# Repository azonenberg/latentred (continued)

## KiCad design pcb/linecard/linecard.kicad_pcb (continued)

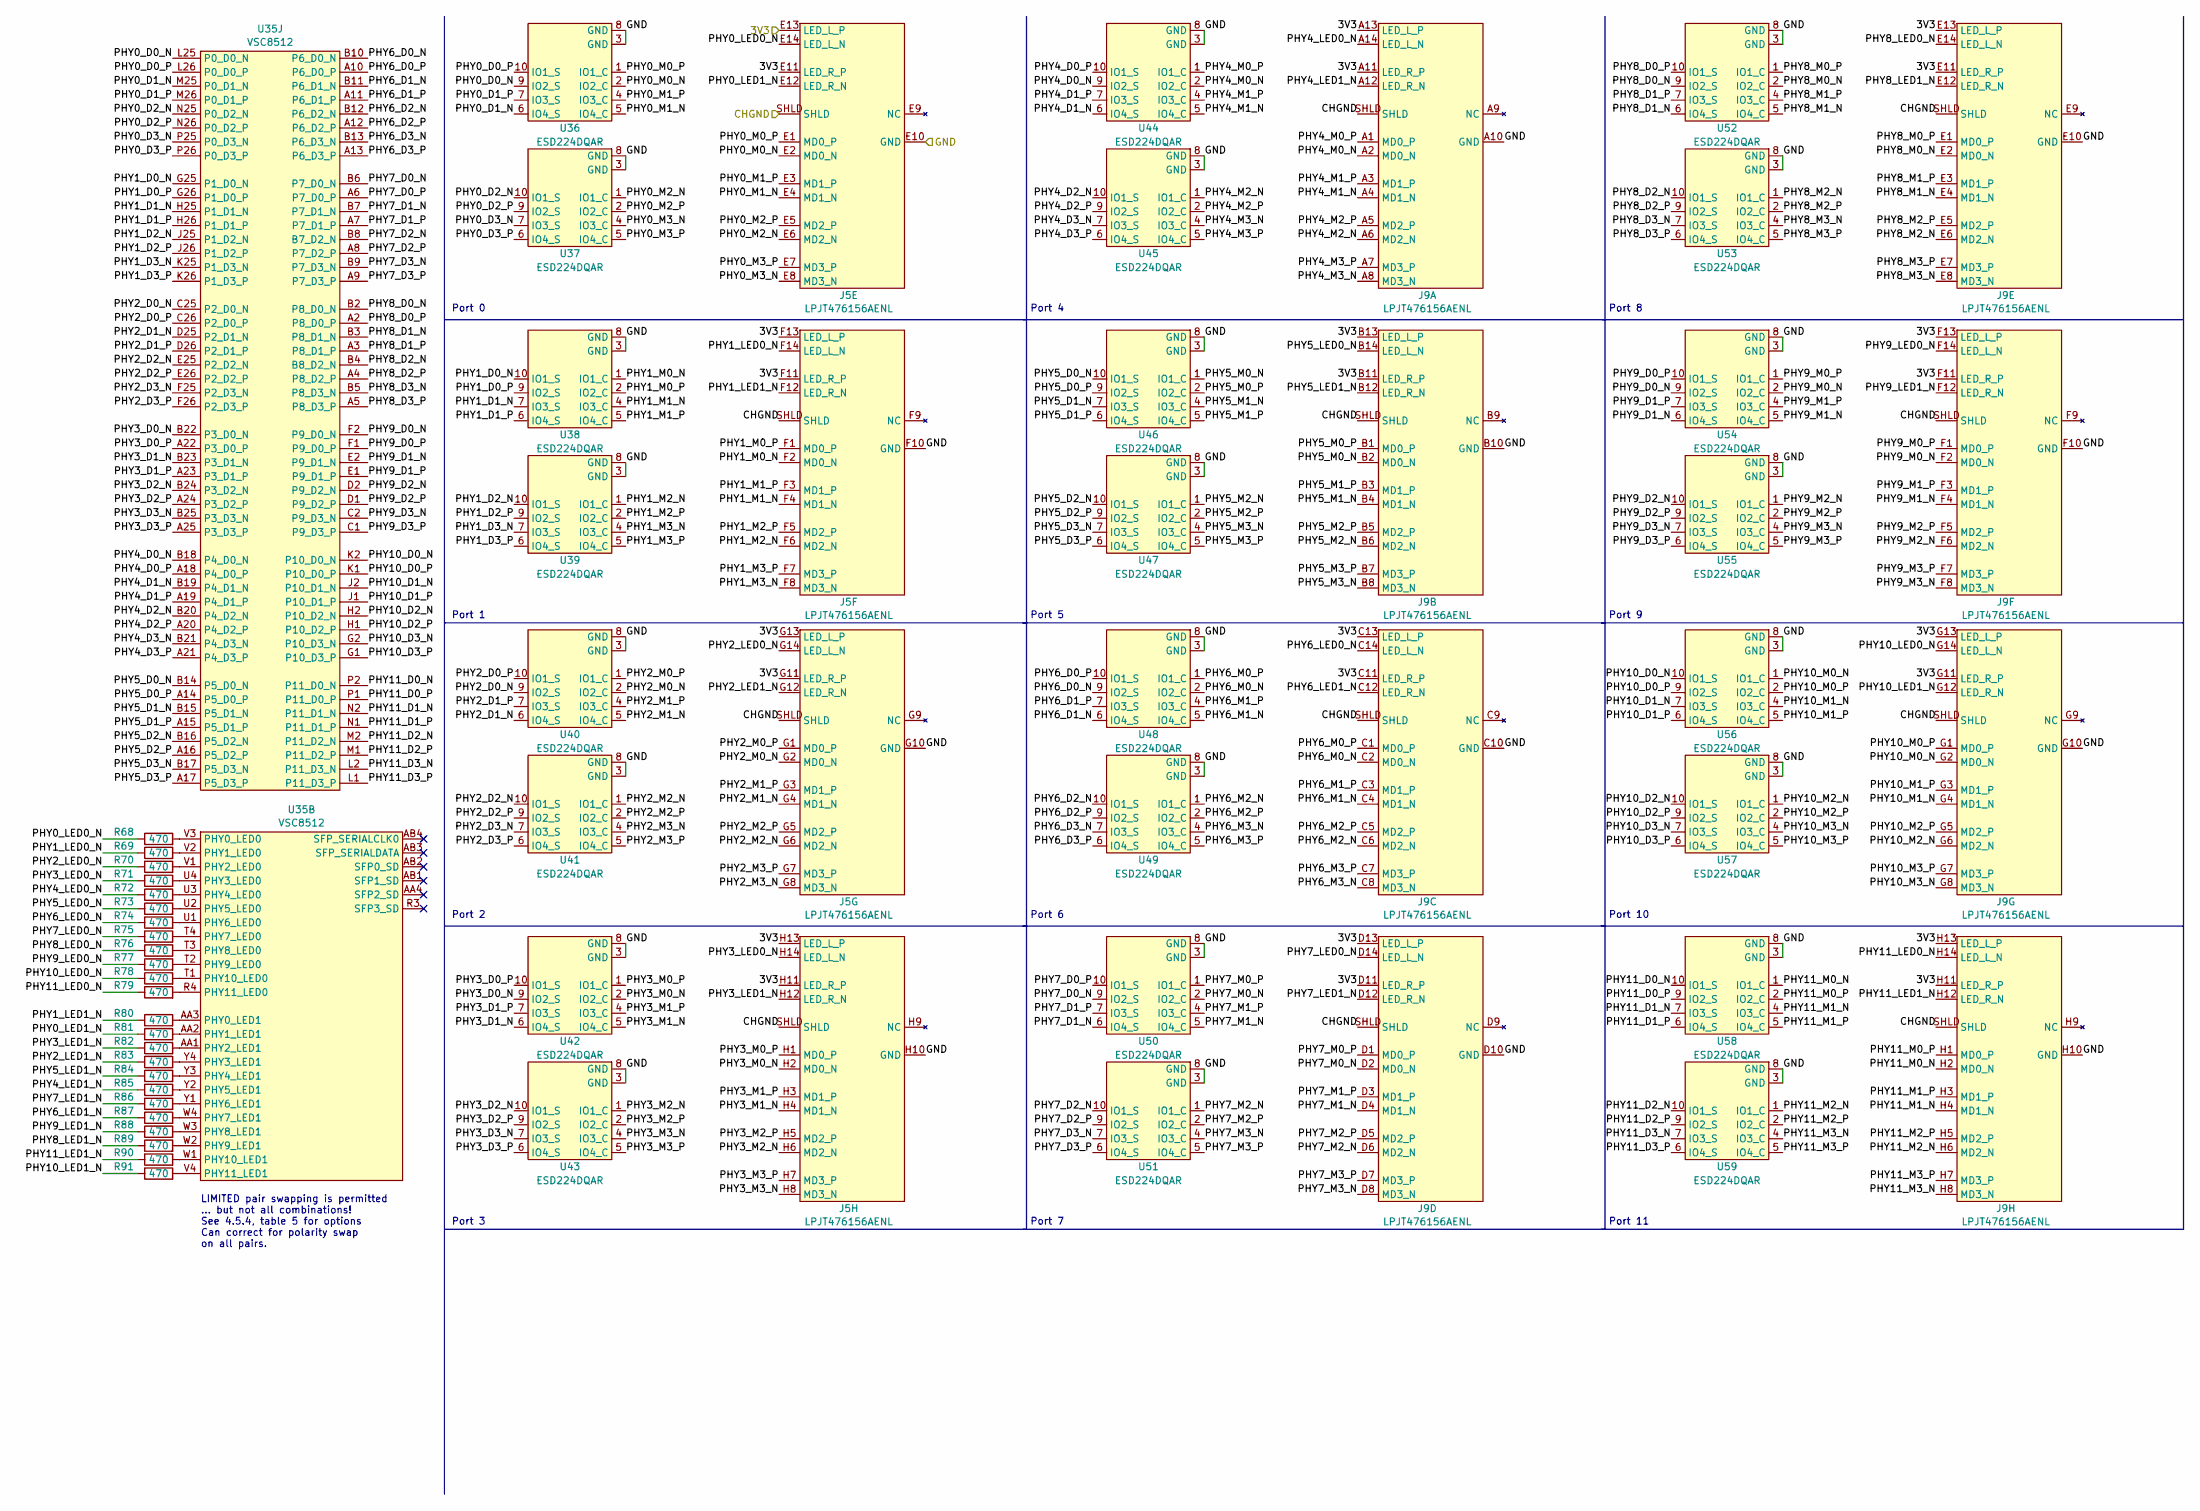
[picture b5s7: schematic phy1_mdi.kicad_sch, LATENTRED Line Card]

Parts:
J5, J9: LPJT476156AENL; CONN_LINKPP_LPJT476156AENL
R68, R69, R70, R71, R72, R73, R74, R75, R76, R77, R78, R79, R80, R81, R82, R83, R84, R85, R86, R87, R88, R89, R90, R91: 470; EIA_0402_RES_NOSILK
U35: VSC8512; BGA_676_27x27_FULLARRAY_1MM_FFG676
U36, U37, U38, U39, U40, U41, U42, U43, U44, U45, U46, U47, U48, U49, U50, U51, U52, U53, U54, U55, U56, U57, U58, U59: ESD224DQAR; DFN_10_0.5MM_2.5x1MM_TI_DQA

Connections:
/3V3: J5.E11 (LED_R_P), J5.E13 (LED_L_P), J5.F11 (LED_R_P), J5.F13 (LED_L_P), J5.G11 (LED_R_P), J5.G13 (LED_L_P), J5.H11 (LED_R_P), J5.H13 (LED_L_P), J9.A11 (LED_R_P), J9.A13 (LED_L_P), J9.B11 (LED_R_P), J9.B13 (LED_L_P), J9.C11 (LED_R_P), J9.C13 (LED_L_P), J9.D11 (LED_R_P), J9.D13 (LED_L_P), J9.E11 (LED_R_P), J9.E13 (LED_L_P), J9.F11 (LED_R_P), J9.F13 (LED_L_P), J9.G11 (LED_R_P), J9.G13 (LED_L_P), J9.H11 (LED_R_P), J9.H13 (LED_L_P); also elsewhere on the board
/PHY 1 MDI/PHY0_D0_N: U35.L25 (P0_D0_N), U36.9 (IO2_S)
/PHY 1 MDI/PHY0_D0_P: U35.L26 (P0_D0_P), U36.10 (IO1_S)
/PHY 1 MDI/PHY0_D1_N: U35.M25 (P0_D1_N), U36.6 (IO4_S)
/PHY 1 MDI/PHY0_D1_P: U35.M26 (P0_D1_P), U36.7 (IO3_S)
/PHY 1 MDI/PHY0_D2_N: U35.N25 (P0_D2_N), U37.10 (IO1_S)
/PHY 1 MDI/PHY0_D2_P: U35.N26 (P0_D2_P), U37.9 (IO2_S)
/PHY 1 MDI/PHY0_D3_N: U35.P25 (P0_D3_N), U37.7 (IO3_S)
/PHY 1 MDI/PHY0_D3_P: U35.P26 (P0_D3_P), U37.6 (IO4_S)
/PHY 1 MDI/PHY0_LED0_N: J5.E14 (LED_L_N), R68.1
/PHY 1 MDI/PHY0_LED1_N: J5.E12 (LED_R_N), R81.1
/PHY 1 MDI/PHY0_M0_N: J5.E2 (MD0_N), U36.2 (IO2_C)
/PHY 1 MDI/PHY0_M0_P: J5.E1 (MD0_P), U36.1 (IO1_C)
/PHY 1 MDI/PHY0_M1_N: J5.E4 (MD1_N), U36.5 (IO4_C)
/PHY 1 MDI/PHY0_M1_P: J5.E3 (MD1_P), U36.4 (IO3_C)
/PHY 1 MDI/PHY0_M2_N: J5.E6 (MD2_N), U37.1 (IO1_C)
/PHY 1 MDI/PHY0_M2_P: J5.E5 (MD2_P), U37.2 (IO2_C)
/PHY 1 MDI/PHY0_M3_N: J5.E8 (MD3_N), U37.4 (IO3_C)
/PHY 1 MDI/PHY0_M3_P: J5.E7 (MD3_P), U37.5 (IO4_C)
/PHY 1 MDI/PHY1_D0_N: U35.G25 (P1_D0_N), U38.10 (IO1_S)
/PHY 1 MDI/PHY1_D0_P: U35.G26 (P1_D0_P), U38.9 (IO2_S)
/PHY 1 MDI/PHY1_D1_N: U35.H25 (P1_D1_N), U38.7 (IO3_S)
/PHY 1 MDI/PHY1_D1_P: U35.H26 (P1_D1_P), U38.6 (IO4_S)
/PHY 1 MDI/PHY1_D2_N: U35.J25 (P1_D2_N), U39.10 (IO1_S)
/PHY 1 MDI/PHY1_D2_P: U35.J26 (P1_D2_P), U39.9 (IO2_S)
/PHY 1 MDI/PHY1_D3_N: U35.K25 (P1_D3_N), U39.7 (IO3_S)
/PHY 1 MDI/PHY1_D3_P: U35.K26 (P1_D3_P), U39.6 (IO4_S)
/PHY 1 MDI/PHY1_LED0_N: J5.F14 (LED_L_N), R69.1
/PHY 1 MDI/PHY1_LED1_N: J5.F12 (LED_R_N), R80.1
/PHY 1 MDI/PHY1_M0_N: J5.F2 (MD0_N), U38.1 (IO1_C)
/PHY 1 MDI/PHY1_M0_P: J5.F1 (MD0_P), U38.2 (IO2_C)
/PHY 1 MDI/PHY1_M1_N: J5.F4 (MD1_N), U38.4 (IO3_C)
/PHY 1 MDI/PHY1_M1_P: J5.F3 (MD1_P), U38.5 (IO4_C)
/PHY 1 MDI/PHY1_M2_N: J5.F6 (MD2_N), U39.1 (IO1_C)
/PHY 1 MDI/PHY1_M2_P: J5.F5 (MD2_P), U39.2 (IO2_C)
/PHY 1 MDI/PHY1_M3_N: J5.F8 (MD3_N), U39.4 (IO3_C)
/PHY 1 MDI/PHY1_M3_P: J5.F7 (MD3_P), U39.5 (IO4_C)
/PHY 1 MDI/PHY2_D0_N: U35.C25 (P2_D0_N), U40.9 (IO2_S)
/PHY 1 MDI/PHY2_D0_P: U35.C26 (P2_D0_P), U40.10 (IO1_S)
/PHY 1 MDI/PHY2_D1_N: U35.D25 (P2_D1_N), U40.6 (IO4_S)
/PHY 1 MDI/PHY2_D1_P: U35.D26 (P2_D1_P), U40.7 (IO3_S)
/PHY 1 MDI/PHY2_D2_N: U35.E25 (P2_D2_N), U41.10 (IO1_S)
/PHY 1 MDI/PHY2_D2_P: U35.E26 (P2_D2_P), U41.9 (IO2_S)
/PHY 1 MDI/PHY2_D3_N: U35.F25 (P2_D3_N), U41.7 (IO3_S)
/PHY 1 MDI/PHY2_D3_P: U35.F26 (P2_D3_P), U41.6 (IO4_S)
/PHY 1 MDI/PHY2_LED0_N: J5.G14 (LED_L_N), R70.1
/PHY 1 MDI/PHY2_LED1_N: J5.G12 (LED_R_N), R83.1
/PHY 1 MDI/PHY2_M0_N: J5.G2 (MD0_N), U40.2 (IO2_C)
/PHY 1 MDI/PHY2_M0_P: J5.G1 (MD0_P), U40.1 (IO1_C)
/PHY 1 MDI/PHY2_M1_N: J5.G4 (MD1_N), U40.5 (IO4_C)
/PHY 1 MDI/PHY2_M1_P: J5.G3 (MD1_P), U40.4 (IO3_C)
/PHY 1 MDI/PHY2_M2_N: J5.G6 (MD2_N), U41.1 (IO1_C)
/PHY 1 MDI/PHY2_M2_P: J5.G5 (MD2_P), U41.2 (IO2_C)
/PHY 1 MDI/PHY2_M3_N: J5.G8 (MD3_N), U41.4 (IO3_C)
/PHY 1 MDI/PHY2_M3_P: J5.G7 (MD3_P), U41.5 (IO4_C)
/PHY 1 MDI/PHY3_D0_N: U35.B22 (P3_D0_N), U42.9 (IO2_S)
/PHY 1 MDI/PHY3_D0_P: U35.A22 (P3_D0_P), U42.10 (IO1_S)
/PHY 1 MDI/PHY3_D1_N: U35.B23 (P3_D1_N), U42.6 (IO4_S)
/PHY 1 MDI/PHY3_D1_P: U35.A23 (P3_D1_P), U42.7 (IO3_S)
/PHY 1 MDI/PHY3_D2_N: U35.B24 (P3_D2_N), U43.10 (IO1_S)
/PHY 1 MDI/PHY3_D2_P: U35.A24 (P3_D2_P), U43.9 (IO2_S)
/PHY 1 MDI/PHY3_D3_N: U35.B25 (P3_D3_N), U43.7 (IO3_S)
/PHY 1 MDI/PHY3_D3_P: U35.A25 (P3_D3_P), U43.6 (IO4_S)
/PHY 1 MDI/PHY3_LED0_N: J5.H14 (LED_L_N), R71.1
/PHY 1 MDI/PHY3_LED1_N: J5.H12 (LED_R_N), R82.1
/PHY 1 MDI/PHY3_M0_N: J5.H2 (MD0_N), U42.2 (IO2_C)
/PHY 1 MDI/PHY3_M0_P: J5.H1 (MD0_P), U42.1 (IO1_C)
/PHY 1 MDI/PHY3_M1_N: J5.H4 (MD1_N), U42.5 (IO4_C)
/PHY 1 MDI/PHY3_M1_P: J5.H3 (MD1_P), U42.4 (IO3_C)
/PHY 1 MDI/PHY3_M2_N: J5.H6 (MD2_N), U43.1 (IO1_C)
/PHY 1 MDI/PHY3_M2_P: J5.H5 (MD2_P), U43.2 (IO2_C)
/PHY 1 MDI/PHY3_M3_N: J5.H8 (MD3_N), U43.4 (IO3_C)
/PHY 1 MDI/PHY3_M3_P: J5.H7 (MD3_P), U43.5 (IO4_C)
/PHY 1 MDI/PHY4_D0_N: U35.B18 (P4_D0_N), U44.9 (IO2_S)
/PHY 1 MDI/PHY4_D0_P: U35.A18 (P4_D0_P), U44.10 (IO1_S)
/PHY 1 MDI/PHY4_D1_N: U35.B19 (P4_D1_N), U44.6 (IO4_S)
/PHY 1 MDI/PHY4_D1_P: U35.A19 (P4_D1_P), U44.7 (IO3_S)
/PHY 1 MDI/PHY4_D2_N: U35.B20 (P4_D2_N), U45.10 (IO1_S)
/PHY 1 MDI/PHY4_D2_P: U35.A20 (P4_D2_P), U45.9 (IO2_S)
/PHY 1 MDI/PHY4_D3_N: U35.B21 (P4_D3_N), U45.7 (IO3_S)
/PHY 1 MDI/PHY4_D3_P: U35.A21 (P4_D3_P), U45.6 (IO4_S)
/PHY 1 MDI/PHY4_LED0_N: J9.A14 (LED_L_N), R72.1
/PHY 1 MDI/PHY4_LED1_N: J9.A12 (LED_R_N), R85.1
/PHY 1 MDI/PHY4_M0_N: J9.A2 (MD0_N), U44.2 (IO2_C)
/PHY 1 MDI/PHY4_M0_P: J9.A1 (MD0_P), U44.1 (IO1_C)
/PHY 1 MDI/PHY4_M1_N: J9.A4 (MD1_N), U44.5 (IO4_C)
/PHY 1 MDI/PHY4_M1_P: J9.A3 (MD1_P), U44.4 (IO3_C)
/PHY 1 MDI/PHY4_M2_N: J9.A6 (MD2_N), U45.1 (IO1_C)
/PHY 1 MDI/PHY4_M2_P: J9.A5 (MD2_P), U45.2 (IO2_C)
/PHY 1 MDI/PHY4_M3_N: J9.A8 (MD3_N), U45.4 (IO3_C)
/PHY 1 MDI/PHY4_M3_P: J9.A7 (MD3_P), U45.5 (IO4_C)
/PHY 1 MDI/PHY5_D0_N: U35.B14 (P5_D0_N), U46.10 (IO1_S)
/PHY 1 MDI/PHY5_D0_P: U35.A14 (P5_D0_P), U46.9 (IO2_S)
/PHY 1 MDI/PHY5_D1_N: U35.B15 (P5_D1_N), U46.7 (IO3_S)
/PHY 1 MDI/PHY5_D1_P: U35.A15 (P5_D1_P), U46.6 (IO4_S)
/PHY 1 MDI/PHY5_D2_N: U35.B16 (P5_D2_N), U47.10 (IO1_S)
/PHY 1 MDI/PHY5_D2_P: U35.A16 (P5_D2_P), U47.9 (IO2_S)
/PHY 1 MDI/PHY5_D3_N: U35.B17 (P5_D3_N), U47.7 (IO3_S)
/PHY 1 MDI/PHY5_D3_P: U35.A17 (P5_D3_P), U47.6 (IO4_S)
/PHY 1 MDI/PHY5_LED0_N: J9.B14 (LED_L_N), R73.1
/PHY 1 MDI/PHY5_LED1_N: J9.B12 (LED_R_N), R84.1
/PHY 1 MDI/PHY5_M0_N: J9.B2 (MD0_N), U46.1 (IO1_C)
/PHY 1 MDI/PHY5_M0_P: J9.B1 (MD0_P), U46.2 (IO2_C)
/PHY 1 MDI/PHY5_M1_N: J9.B4 (MD1_N), U46.4 (IO3_C)
/PHY 1 MDI/PHY5_M1_P: J9.B3 (MD1_P), U46.5 (IO4_C)
/PHY 1 MDI/PHY5_M2_N: J9.B6 (MD2_N), U47.1 (IO1_C)
/PHY 1 MDI/PHY5_M2_P: J9.B5 (MD2_P), U47.2 (IO2_C)
/PHY 1 MDI/PHY5_M3_N: J9.B8 (MD3_N), U47.4 (IO3_C)
/PHY 1 MDI/PHY5_M3_P: J9.B7 (MD3_P), U47.5 (IO4_C)
/PHY 1 MDI/PHY6_D0_N: U35.B10 (P6_D0_N), U48.9 (IO2_S)
/PHY 1 MDI/PHY6_D0_P: U35.A10 (P6_D0_P), U48.10 (IO1_S)
/PHY 1 MDI/PHY6_D1_N: U35.B11 (P6_D1_N), U48.6 (IO4_S)
/PHY 1 MDI/PHY6_D1_P: U35.A11 (P6_D1_P), U48.7 (IO3_S)
/PHY 1 MDI/PHY6_D2_N: U35.B12 (P6_D2_N), U49.10 (IO1_S)
/PHY 1 MDI/PHY6_D2_P: U35.A12 (P6_D2_P), U49.9 (IO2_S)
/PHY 1 MDI/PHY6_D3_N: U35.B13 (P6_D3_N), U49.7 (IO3_S)
/PHY 1 MDI/PHY6_D3_P: U35.A13 (P6_D3_P), U49.6 (IO4_S)
/PHY 1 MDI/PHY6_LED0_N: J9.C14 (LED_L_N), R74.1
/PHY 1 MDI/PHY6_LED1_N: J9.C12 (LED_R_N), R87.1
/PHY 1 MDI/PHY6_M0_N: J9.C2 (MD0_N), U48.2 (IO2_C)
/PHY 1 MDI/PHY6_M0_P: J9.C1 (MD0_P), U48.1 (IO1_C)
/PHY 1 MDI/PHY6_M1_N: J9.C4 (MD1_N), U48.5 (IO4_C)
/PHY 1 MDI/PHY6_M1_P: J9.C3 (MD1_P), U48.4 (IO3_C)
/PHY 1 MDI/PHY6_M2_N: J9.C6 (MD2_N), U49.1 (IO1_C)
/PHY 1 MDI/PHY6_M2_P: J9.C5 (MD2_P), U49.2 (IO2_C)
/PHY 1 MDI/PHY6_M3_N: J9.C8 (MD3_N), U49.4 (IO3_C)
/PHY 1 MDI/PHY6_M3_P: J9.C7 (MD3_P), U49.5 (IO4_C)
/PHY 1 MDI/PHY7_D0_N: U35.B6 (P7_D0_N), U50.9 (IO2_S)
/PHY 1 MDI/PHY7_D0_P: U35.A6 (P7_D0_P), U50.10 (IO1_S)
/PHY 1 MDI/PHY7_D1_N: U35.B7 (P7_D1_N), U50.6 (IO4_S)
/PHY 1 MDI/PHY7_D1_P: U35.A7 (P7_D1_P), U50.7 (IO3_S)
/PHY 1 MDI/PHY7_D2_N: U35.B8 (B7_D2_N), U51.10 (IO1_S)
/PHY 1 MDI/PHY7_D2_P: U35.A8 (P7_D2_P), U51.9 (IO2_S)
/PHY 1 MDI/PHY7_D3_N: U35.B9 (P7_D3_N), U51.7 (IO3_S)
/PHY 1 MDI/PHY7_D3_P: U35.A9 (P7_D3_P), U51.6 (IO4_S)
/PHY 1 MDI/PHY7_LED0_N: J9.D14 (LED_L_N), R75.1
/PHY 1 MDI/PHY7_LED1_N: J9.D12 (LED_R_N), R86.1
/PHY 1 MDI/PHY7_M0_N: J9.D2 (MD0_N), U50.2 (IO2_C)
/PHY 1 MDI/PHY7_M0_P: J9.D1 (MD0_P), U50.1 (IO1_C)
/PHY 1 MDI/PHY7_M1_N: J9.D4 (MD1_N), U50.5 (IO4_C)
/PHY 1 MDI/PHY7_M1_P: J9.D3 (MD1_P), U50.4 (IO3_C)
/PHY 1 MDI/PHY7_M2_N: J9.D6 (MD2_N), U51.1 (IO1_C)
/PHY 1 MDI/PHY7_M2_P: J9.D5 (MD2_P), U51.2 (IO2_C)
/PHY 1 MDI/PHY7_M3_N: J9.D8 (MD3_N), U51.4 (IO3_C)
/PHY 1 MDI/PHY7_M3_P: J9.D7 (MD3_P), U51.5 (IO4_C)
/PHY 1 MDI/PHY8_D0_N: U35.B2 (P8_D0_N), U52.9 (IO2_S)
/PHY 1 MDI/PHY8_D0_P: U35.A2 (P8_D0_P), U52.10 (IO1_S)
/PHY 1 MDI/PHY8_D1_N: U35.B3 (P8_D1_N), U52.6 (IO4_S)
/PHY 1 MDI/PHY8_D1_P: U35.A3 (P8_D1_P), U52.7 (IO3_S)
/PHY 1 MDI/PHY8_D2_N: U35.B4 (B8_D2_N), U53.10 (IO1_S)
/PHY 1 MDI/PHY8_D2_P: U35.A4 (P8_D2_P), U53.9 (IO2_S)
/PHY 1 MDI/PHY8_D3_N: U35.B5 (P8_D3_N), U53.7 (IO3_S)
/PHY 1 MDI/PHY8_D3_P: U35.A5 (P8_D3_P), U53.6 (IO4_S)
/PHY 1 MDI/PHY8_LED0_N: J9.E14 (LED_L_N), R76.1
/PHY 1 MDI/PHY8_LED1_N: J9.E12 (LED_R_N), R89.1
/PHY 1 MDI/PHY8_M0_N: J9.E2 (MD0_N), U52.2 (IO2_C)
/PHY 1 MDI/PHY8_M0_P: J9.E1 (MD0_P), U52.1 (IO1_C)
/PHY 1 MDI/PHY8_M1_N: J9.E4 (MD1_N), U52.5 (IO4_C)
/PHY 1 MDI/PHY8_M1_P: J9.E3 (MD1_P), U52.4 (IO3_C)
/PHY 1 MDI/PHY8_M2_N: J9.E6 (MD2_N), U53.1 (IO1_C)
/PHY 1 MDI/PHY8_M2_P: J9.E5 (MD2_P), U53.2 (IO2_C)
/PHY 1 MDI/PHY8_M3_N: J9.E8 (MD3_N), U53.4 (IO3_C)
/PHY 1 MDI/PHY8_M3_P: J9.E7 (MD3_P), U53.5 (IO4_C)
/PHY 1 MDI/PHY9_D0_N: U35.F2 (P9_D0_N), U54.9 (IO2_S)
/PHY 1 MDI/PHY9_D0_P: U35.F1 (P9_D0_P), U54.10 (IO1_S)
/PHY 1 MDI/PHY9_D1_N: U35.E2 (P9_D1_N), U54.6 (IO4_S)
/PHY 1 MDI/PHY9_D1_P: U35.E1 (P9_D1_P), U54.7 (IO3_S)
/PHY 1 MDI/PHY9_D2_N: U35.D2 (P9_D2_N), U55.10 (IO1_S)
/PHY 1 MDI/PHY9_D2_P: U35.D1 (P9_D2_P), U55.9 (IO2_S)
/PHY 1 MDI/PHY9_D3_N: U35.C2 (P9_D3_N), U55.7 (IO3_S)
/PHY 1 MDI/PHY9_D3_P: U35.C1 (P9_D3_P), U55.6 (IO4_S)
/PHY 1 MDI/PHY9_LED0_N: J9.F14 (LED_L_N), R77.1
/PHY 1 MDI/PHY9_LED1_N: J9.F12 (LED_R_N), R88.1
/PHY 1 MDI/PHY9_M0_N: J9.F2 (MD0_N), U54.2 (IO2_C)
/PHY 1 MDI/PHY9_M0_P: J9.F1 (MD0_P), U54.1 (IO1_C)
/PHY 1 MDI/PHY9_M1_N: J9.F4 (MD1_N), U54.5 (IO4_C)
/PHY 1 MDI/PHY9_M1_P: J9.F3 (MD1_P), U54.4 (IO3_C)
/PHY 1 MDI/PHY9_M2_N: J9.F6 (MD2_N), U55.1 (IO1_C)
/PHY 1 MDI/PHY9_M2_P: J9.F5 (MD2_P), U55.2 (IO2_C)
/PHY 1 MDI/PHY9_M3_N: J9.F8 (MD3_N), U55.4 (IO3_C)
/PHY 1 MDI/PHY9_M3_P: J9.F7 (MD3_P), U55.5 (IO4_C)
/PHY 1 MDI/PHY10_D0_N: U35.K2 (P10_D0_N), U56.10 (IO1_S)
/PHY 1 MDI/PHY10_D0_P: U35.K1 (P10_D0_P), U56.9 (IO2_S)
/PHY 1 MDI/PHY10_D1_N: U35.J2 (P10_D1_N), U56.7 (IO3_S)
/PHY 1 MDI/PHY10_D1_P: U35.J1 (P10_D1_P), U56.6 (IO4_S)
/PHY 1 MDI/PHY10_D2_N: U35.H2 (P10_D2_N), U57.10 (IO1_S)
/PHY 1 MDI/PHY10_D2_P: U35.H1 (P10_D2_P), U57.9 (IO2_S)
/PHY 1 MDI/PHY10_D3_N: U35.G2 (P10_D3_N), U57.7 (IO3_S)
/PHY 1 MDI/PHY10_D3_P: U35.G1 (P10_D3_P), U57.6 (IO4_S)
/PHY 1 MDI/PHY10_LED0_N: J9.G14 (LED_L_N), R78.1
/PHY 1 MDI/PHY10_LED1_N: J9.G12 (LED_R_N), R91.1
/PHY 1 MDI/PHY10_M0_N: J9.G2 (MD0_N), U56.1 (IO1_C)
/PHY 1 MDI/PHY10_M0_P: J9.G1 (MD0_P), U56.2 (IO2_C)
/PHY 1 MDI/PHY10_M1_N: J9.G4 (MD1_N), U56.4 (IO3_C)
/PHY 1 MDI/PHY10_M1_P: J9.G3 (MD1_P), U56.5 (IO4_C)
/PHY 1 MDI/PHY10_M2_N: J9.G6 (MD2_N), U57.1 (IO1_C)
/PHY 1 MDI/PHY10_M2_P: J9.G5 (MD2_P), U57.2 (IO2_C)
/PHY 1 MDI/PHY10_M3_N: J9.G8 (MD3_N), U57.4 (IO3_C)
/PHY 1 MDI/PHY10_M3_P: J9.G7 (MD3_P), U57.5 (IO4_C)
/PHY 1 MDI/PHY11_D0_N: U35.P2 (P11_D0_N), U58.10 (IO1_S)
/PHY 1 MDI/PHY11_D0_P: U35.P1 (P11_D0_P), U58.9 (IO2_S)
/PHY 1 MDI/PHY11_D1_N: U35.N2 (P11_D1_N), U58.7 (IO3_S)
/PHY 1 MDI/PHY11_D1_P: U35.N1 (P11_D1_P), U58.6 (IO4_S)
/PHY 1 MDI/PHY11_D2_N: U35.M2 (P11_D2_N), U59.10 (IO1_S)
/PHY 1 MDI/PHY11_D2_P: U35.M1 (P11_D2_P), U59.9 (IO2_S)
/PHY 1 MDI/PHY11_D3_N: U35.L2 (P11_D3_N), U59.7 (IO3_S)
/PHY 1 MDI/PHY11_D3_P: U35.L1 (P11_D3_P), U59.6 (IO4_S)
/PHY 1 MDI/PHY11_LED0_N: J9.H14 (LED_L_N), R79.1
/PHY 1 MDI/PHY11_LED1_N: J9.H12 (LED_R_N), R90.1
/PHY 1 MDI/PHY11_M0_N: J9.H2 (MD0_N), U58.1 (IO1_C)
/PHY 1 MDI/PHY11_M0_P: J9.H1 (MD0_P), U58.2 (IO2_C)
/PHY 1 MDI/PHY11_M1_N: J9.H4 (MD1_N), U58.4 (IO3_C)
/PHY 1 MDI/PHY11_M1_P: J9.H3 (MD1_P), U58.5 (IO4_C)
/PHY 1 MDI/PHY11_M2_N: J9.H6 (MD2_N), U59.1 (IO1_C)
/PHY 1 MDI/PHY11_M2_P: J9.H5 (MD2_P), U59.2 (IO2_C)
/PHY 1 MDI/PHY11_M3_N: J9.H8 (MD3_N), U59.4 (IO3_C)
/PHY 1 MDI/PHY11_M3_P: J9.H7 (MD3_P), U59.5 (IO4_C)
unnamed: R68.2, U35.V3 (PHY0_LED0)
unnamed: R80.2, U35.AA3 (PHY0_LED1)
unnamed: R69.2, U35.V2 (PHY1_LED0)
unnamed: R81.2, U35.AA2 (PHY1_LED1)
unnamed: R70.2, U35.V1 (PHY2_LED0)
unnamed: R82.2, U35.AA1 (PHY2_LED1)
unnamed: R71.2, U35.U4 (PHY3_LED0)
unnamed: R83.2, U35.Y4 (PHY3_LED1)
unnamed: R72.2, U35.U3 (PHY4_LED0)
unnamed: R84.2, U35.Y3 (PHY4_LED1)
unnamed: R73.2, U35.U2 (PHY5_LED0)
unnamed: R85.2, U35.Y2 (PHY5_LED1)
unnamed: R74.2, U35.U1 (PHY6_LED0)
unnamed: R86.2, U35.Y1 (PHY6_LED1)
unnamed: R75.2, U35.T4 (PHY7_LED0)
unnamed: R87.2, U35.W4 (PHY7_LED1)
unnamed: R76.2, U35.T3 (PHY8_LED0)
unnamed: R88.2, U35.W3 (PHY8_LED1)
unnamed: R77.2, U35.T2 (PHY9_LED0)
unnamed: R89.2, U35.W2 (PHY9_LED1)
unnamed: R78.2, U35.T1 (PHY10_LED0)
unnamed: R90.2, U35.W1 (PHY10_LED1)
unnamed: R79.2, U35.R4 (PHY11_LED0)
unnamed: R91.2, U35.V4 (PHY11_LED1)

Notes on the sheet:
Port 1
LIMITED pair swapping is permitted ... but not all combinations! See 4.5.4, table 5 for options Can correct for polarity swap on all pairs.
Port 6
Port 0
Port 8
Port 4
Port 10
Port 11
Port 9
Port 2
Port 3
Port 5
Port 7

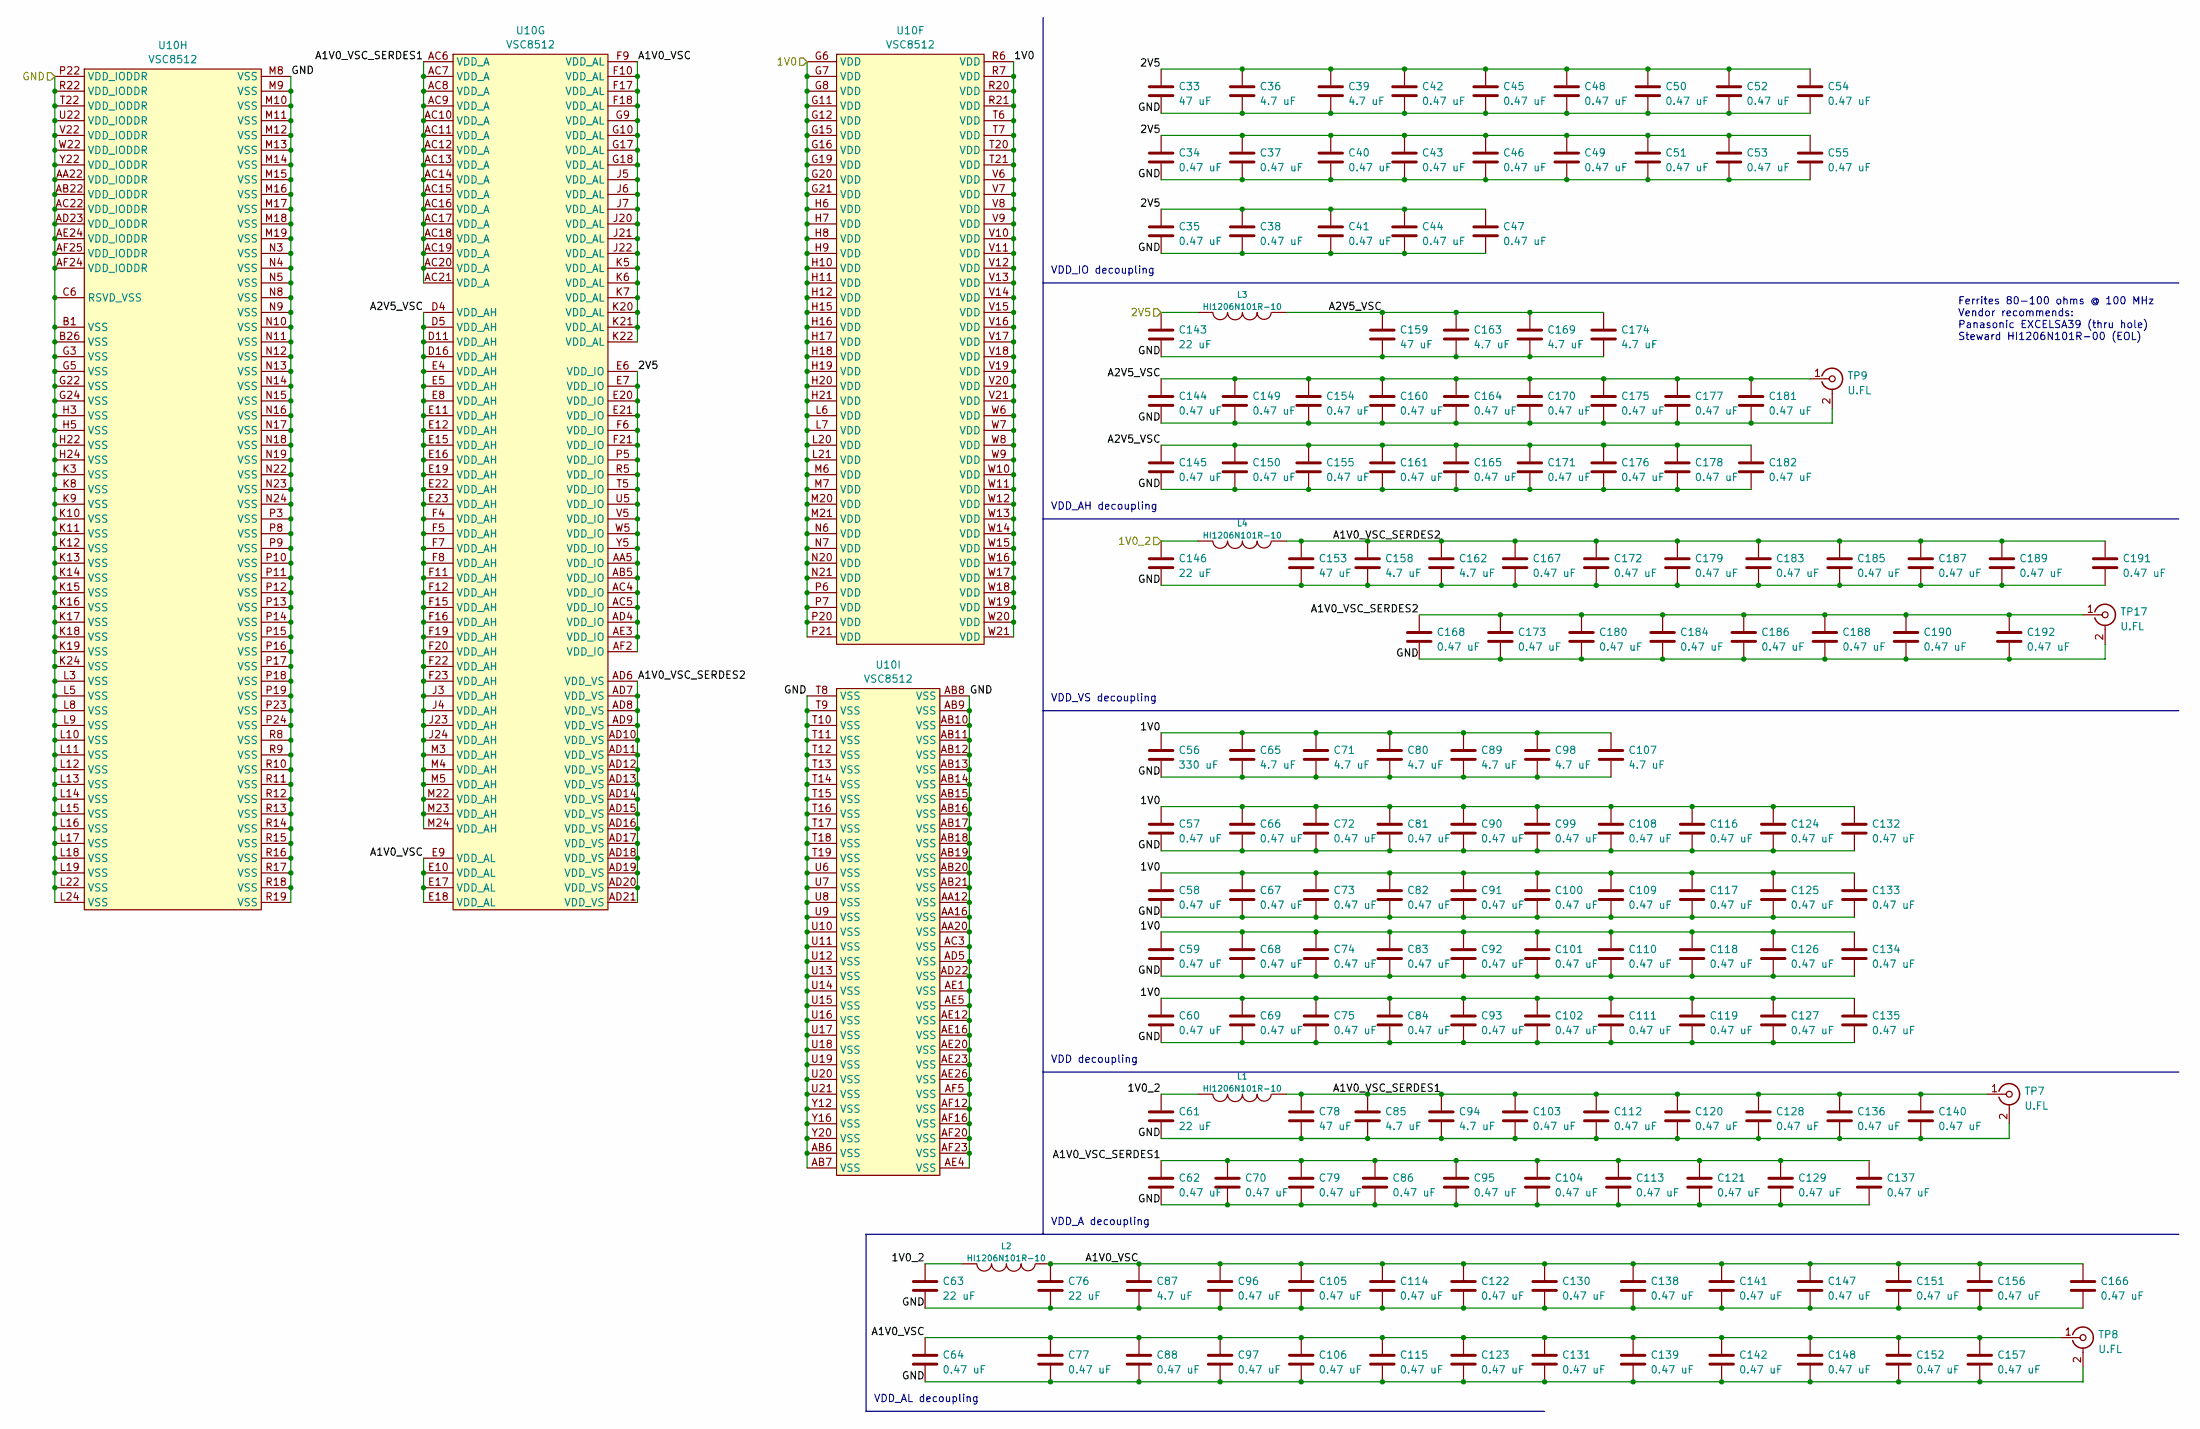
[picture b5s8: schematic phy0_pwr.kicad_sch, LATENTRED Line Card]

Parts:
C33, C78, C153, C159: 47 uF; EIA_1210_CAP_NOSILK
C34, C35, C37, C38, C40, C41, C42, C43, C44, C45, C46, C47, C48, C49, C50, C51, C52, C53, C54, C55, C57, C58, C59, C60, C62, C64, C66, C67, C68, C69, C70, C72, C73, C74, C75, C77, C79, C81, C82, C83, C84, C86, C88, C90, C91, C92, C93, C95, C96, C97, C99, C100, C101, C102, C103, C104, C105, C106, C108, C109, C110, C111, C112, C113, C114, C115, C116, C117, C118, C119, C120, C121, C122, C123, C124, C125, C126, C127, C128, C129, C130, C131, C132, C133, C134, C135, C136, C137, C138, C139, C140, C141, C142, C144, C145, C147, C148, C149, C150, C151, C152, C154, C155, C156, C157, C160, C161, C164, C165, C166, C167, C168, C170, C171, C172, C173, C175, C176, C177, C178, C179, C180, C181, C182, C183, C184, C185, C186, C187, C188, C189, C190, C191, C192: 0.47 uF; EIA_0402_CAP_NOSILK
C36, C39, C65, C71, C80, C85, C87, C89, C94, C98, C107, C158, C162, C163, C169, C174: 4.7 uF; EIA_0603_CAP_NOSILK
C56: 330 uF; EIA_1210_CAP_NOSILK
C61, C63, C76, C146: 22 uF; EIA_0805_CAP_NOSILK
C143: 22 uF; EIA_1206_CAP_NOSILK
L1, L2, L3, L4: HI1206N101R-10; EIA_1206_CAP_NOSILK
TP7, TP8, TP9, TP17: U.FL; CONN_U.FL_TE_1909763-1
U10: VSC8512; BGA_676_27x27_FULLARRAY_1MM_FFG676

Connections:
/1V0: C56.1, C57.1, C58.1, C59.1, C60.1, C65.1, C66.1, C67.1, C68.1, C69.1, C71.1, C72.1, C73.1, C74.1, C75.1, C80.1, C81.1, C82.1, C83.1, C84.1, C89.1, C90.1, C91.1, C92.1, C93.1, C98.1, C99.1, C100.1, C101.1, C102.1, C107.1, C108.1, C109.1, C110.1, C111.1, C116.1, C117.1, C118.1, C119.1, C124.1, C125.1, C126.1, C127.1, C132.1, C133.1, C134.1, C135.1, U10.G6 (VDD), U10.G7 (VDD), U10.G8 (VDD), U10.G11 (VDD), U10.G12 (VDD), U10.G15 (VDD), U10.G16 (VDD), U10.G19 (VDD), U10.G20 (VDD), U10.G21 (VDD), U10.H6 (VDD), U10.H7 (VDD), U10.H8 (VDD), U10.H9 (VDD), U10.H10 (VDD), U10.H11 (VDD), U10.H12 (VDD), U10.H15 (VDD), U10.H16 (VDD), U10.H17 (VDD), U10.H18 (VDD), U10.H19 (VDD), U10.H20 (VDD), U10.H21 (VDD), U10.L6 (VDD), U10.L7 (VDD), U10.L20 (VDD), U10.L21 (VDD), U10.M6 (VDD), U10.M7 (VDD), U10.M20 (VDD), U10.M21 (VDD), U10.N6 (VDD), U10.N7 (VDD), U10.N20 (VDD), U10.N21 (VDD)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; also elsewhere on the board
/1V0_2: C61.1, C63.1, C146.1, L1.2, L2.2, L4.2; also elsewhere on the board
/2V5: C33.1, C34.1, C35.1, C36.1, C37.1, C38.1, C39.1, C40.1, C41.1, C42.1, C43.1, C44.1, C45.1, C46.1, C47.1, C48.1, C49.1, C50.1, C51.1, C52.1, C53.1, C54.1, C55.1, C143.1, L3.2, U10.AA5 (VDD_IO), U10.AB5 (VDD_IO), U10.AC4 (VDD_IO), U10.AC5 (VDD_IO), U10.AD4 (VDD_IO), U10.AE3 (VDD_IO), U10.AF2 (VDD_IO), U10.E6 (VDD_IO), U10.E7 (VDD_IO), U10.E20 (VDD_IO), U10.E21 (VDD_IO), U10.F6 (VDD_IO), U10.F21 (VDD_IO), U10.P5 (VDD_IO), U10.R5 (VDD_IO), U10.T5 (VDD_IO), U10.U5 (VDD_IO), U10.V5 (VDD_IO), U10.W5 (VDD_IO), U10.Y5 (VDD_IO); also elsewhere on the board
/PHY 0 Power/A1V0_VSC: C64.1, C76.1, C77.1, C87.1, C88.1, C96.1, C97.1, C105.1, C106.1, C114.1, C115.1, C122.1, C123.1, C130.1, C131.1, C138.1, C139.1, C141.1, C142.1, C147.1, C148.1, C151.1, C152.1, C156.1, C157.1, C166.1, L2.1, TP8.1 (In), U10.E9 (VDD_AL), U10.E10 (VDD_AL), U10.E17 (VDD_AL), U10.E18 (VDD_AL), U10.F9 (VDD_AL), U10.F10 (VDD_AL), U10.F17 (VDD_AL), U10.F18 (VDD_AL), U10.G9 (VDD_AL), U10.G10 (VDD_AL), U10.G17 (VDD_AL), U10.G18 (VDD_AL), U10.J5 (VDD_AL), U10.J6 (VDD_AL), U10.J7 (VDD_AL), U10.J20 (VDD_AL), U10.J21 (VDD_AL), U10.J22 (VDD_AL), U10.K5 (VDD_AL), U10.K6 (VDD_AL), U10.K7 (VDD_AL), U10.K20 (VDD_AL), U10.K21 (VDD_AL), U10.K22 (VDD_AL)
/PHY 0 Power/A1V0_VSC_SERDES1: C62.1, C70.1, C78.1, C79.1, C85.1, C86.1, C94.1, C95.1, C103.1, C104.1, C112.1, C113.1, C120.1, C121.1, C128.1, C129.1, C136.1, C137.1, C140.1, L1.1, TP7.1 (In), U10.AC6 (VDD_A), U10.AC7 (VDD_A), U10.AC8 (VDD_A), U10.AC9 (VDD_A), U10.AC10 (VDD_A), U10.AC11 (VDD_A), U10.AC12 (VDD_A), U10.AC13 (VDD_A), U10.AC14 (VDD_A), U10.AC15 (VDD_A), U10.AC16 (VDD_A), U10.AC17 (VDD_A), U10.AC18 (VDD_A), U10.AC19 (VDD_A), U10.AC20 (VDD_A), U10.AC21 (VDD_A)
/PHY 0 Power/A1V0_VSC_SERDES2: C153.1, C158.1, C162.1, C167.1, C168.1, C172.1, C173.1, C179.1, C180.1, C183.1, C184.1, C185.1, C186.1, C187.1, C188.1, C189.1, C190.1, C191.1, C192.1, L4.1, TP17.1 (In), U10.AD6 (VDD_VS), U10.AD7 (VDD_VS), U10.AD8 (VDD_VS), U10.AD9 (VDD_VS), U10.AD10 (VDD_VS), U10.AD11 (VDD_VS), U10.AD12 (VDD_VS), U10.AD13 (VDD_VS), U10.AD14 (VDD_VS), U10.AD15 (VDD_VS), U10.AD16 (VDD_VS), U10.AD17 (VDD_VS), U10.AD18 (VDD_VS), U10.AD19 (VDD_VS), U10.AD20 (VDD_VS), U10.AD21 (VDD_VS)
/PHY 0 Power/A2V5_VSC: C144.1, C145.1, C149.1, C150.1, C154.1, C155.1, C159.1, C160.1, C161.1, C163.1, C164.1, C165.1, C169.1, C170.1, C171.1, C174.1, C175.1, C176.1, C177.1, C178.1, C181.1, C182.1, L3.1, TP9.1 (In), U10.D4 (VDD_AH), U10.D5 (VDD_AH), U10.D11 (VDD_AH), U10.D16 (VDD_AH), U10.E4 (VDD_AH), U10.E5 (VDD_AH), U10.E8 (VDD_AH), U10.E11 (VDD_AH), U10.E12 (VDD_AH), U10.E15 (VDD_AH), U10.E16 (VDD_AH), U10.E19 (VDD_AH), U10.E22 (VDD_AH), U10.E23 (VDD_AH), U10.F4 (VDD_AH), U10.F5 (VDD_AH), U10.F7 (VDD_AH), U10.F8 (VDD_AH), U10.F11 (VDD_AH), U10.F12 (VDD_AH), U10.F15 (VDD_AH), U10.F16 (VDD_AH), U10.F19 (VDD_AH), U10.F20 (VDD_AH), U10.F22 (VDD_AH), U10.F23 (VDD_AH), U10.J3 (VDD_AH), U10.J4 (VDD_AH), U10.J23 (VDD_AH), U10.J24 (VDD_AH), U10.M3 (VDD_AH), U10.M4 (VDD_AH), U10.M5 (VDD_AH), U10.M22 (VDD_AH), U10.M23 (VDD_AH), U10.M24 (VDD_AH)

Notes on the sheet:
VDD_A decoupling
Ferrites 80-100 ohms @ 100 MHz Vendor recommends: Panasonic EXCELSA39 (thru hole) Steward HI1206N101R-00 (EOL)
VDD_IO decoupling
VDD_VS decoupling
VDD_AL decoupling
VDD_AH decoupling
VDD decoupling

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
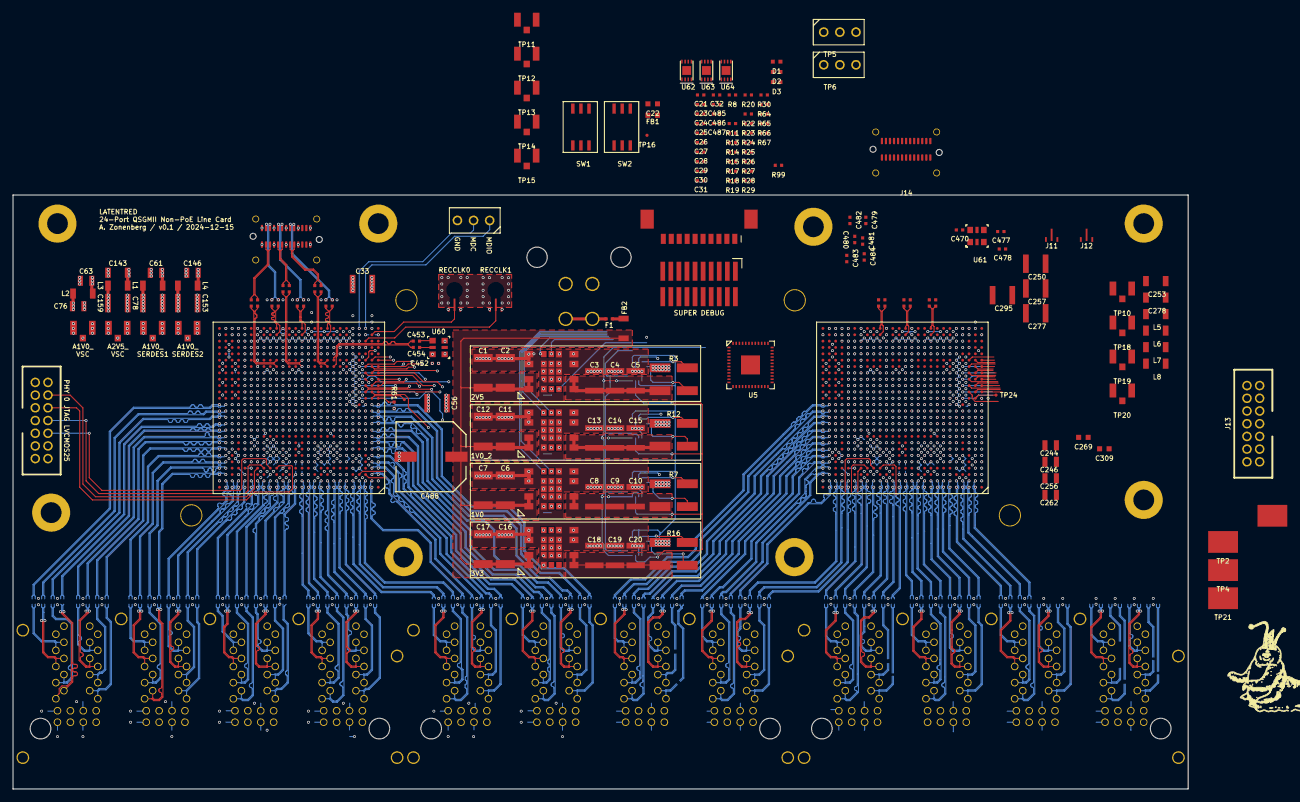
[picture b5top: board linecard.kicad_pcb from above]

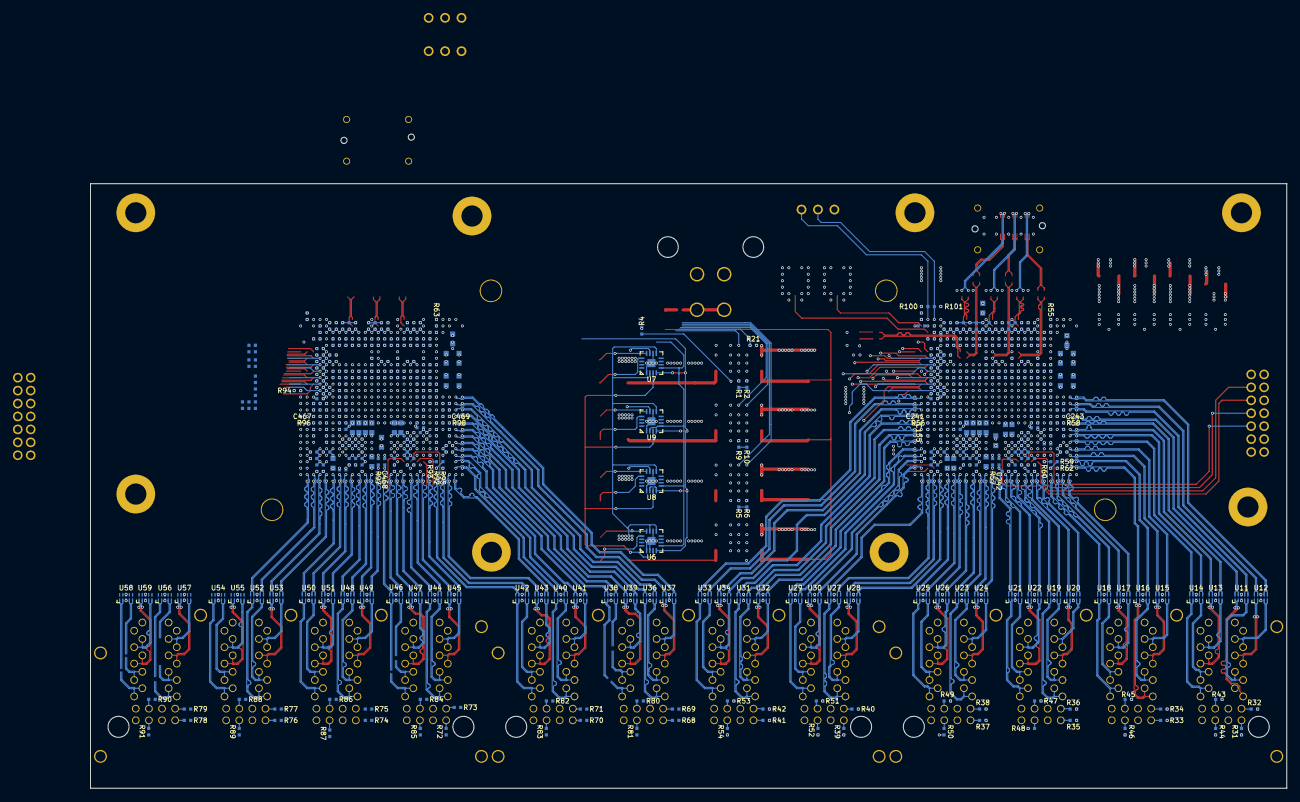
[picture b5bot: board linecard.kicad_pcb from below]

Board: 6 copper layers, 185.0 x 93.5 mm, 623 parts (429 on the bottom side), 656 nets.

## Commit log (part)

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2024-12-09 Initial schematic with power supply and supervisor MCU
2024-12-11 Hopefully finished first PHY
2024-12-11 Finished initial schematic of line card
2024-12-11 Added heatsink, some silkscreen logos, mounting holes, and ground clips
2024-12-12 Finished initial schematic review
2024-12-13 Began layout of first few ports and left VSC8512
2024-12-13 Updated ignores
2024-12-13 Update waiting for new part from vendor
2024-12-13 Initial ESD diode simulation with no cutout and simple 0R model
2024-12-14 COntinued routing baseT pairs on left PHY
2024-12-14 Left half getting close to finished
2024-12-14 Finished routing LEDs to left PHY
2024-12-14 Continued routing left PHY, put right PHY + heatsink in approximately final position
2024-12-14 Finished routing of left PHY
2024-12-15 Preliminary placement of ESD diodes for right PHY
2024-12-16 Began routing right side VSC8512
2024-12-16 Continued routing right hand PHY
2024-12-16 Continued routing right VSC8512
2024-12-16 Continued routing right PHY power. 834 unrouted.
2024-12-16 Continued routing right PHY. 644 unrouted.
2024-12-17 576 unrouted. More decoupling and baseT work on right side PHY. Started LED fanout.
2024-12-17 Initial skeleton of PDU
2024-12-17 Began work on line card power supply
2024-12-17 Continued routing power supply
2024-12-17 Continued power supply routing
2024-12-17 Initial capacitor placement for PHY 1 QSGMII
2024-12-18 Started routing supervisor
2024-12-18 Continued routing supervisor. 293 unrouted.
2024-12-19 Continued tying up loose ends on routing of left side and supervisor
2024-12-19 Added planes, more LED signals, etc
2024-12-19 96 unrouted, all LEDs hooked up
2024-12-19 Continued power routing on right PHY
2024-12-19 Continued routing right PHY
2024-12-19 Updating file: linecard.kicad_pcb with current fully routed design
2024-12-19 Added zone fills
2024-12-19 Initial simulations for QSGMII connector launch
2024-12-20 Ground plane cutouts on line card
2024-12-20 More simulations of line card QSGMII launches
2024-12-20 Updated line card layout after some track cleanup
2024-12-20 Layout is now DRC-clean
2024-12-20 Added stitching vias
2024-12-21 More tuning of cutouts
2024-12-21 Added more simulations
2024-12-21 Optimized routing of right PHY LEDs
2024-12-21 More routing cleanup
2024-12-22 Updated board design with 90/110 um diffpairs
2024-12-22 Removed simulations based on wrong diffpair geometry
2024-12-22 Next round of sims
2024-12-23 Hopefully final layout ready to fab pending final sim runs
2024-12-24 Updated ignore properties
2024-12-24 More last minute silkscreen tweaks
2024-12-27 Removed sims based on original stackup
2024-12-27 Updated fab notes with new stackup from Multech
2024-12-30 Updated QSGMII sims for working gerbers
2024-12-30 Initial version of PDU board is done, ready for review
2024-12-30 Finished PDU design, ready for fab
2025-01-11 Initial schematic for lcbringup
2025-01-15 Continued lcbringup layout
2025-01-16 Continued line card bringup board
2025-01-17 Added a lot of submodules
2025-01-17 PDU: fixed incorrect I2C address note in schematic
2025-01-17 Initial directory structure for line card firmware
2025-01-19 Added etlcpp submodule
2025-01-19 Continued lcbringup layout on ARF6 area
2025-01-20 Conitnued lcbringup layout, power supply is now floorplanned
2025-01-21 Finished initial lcbringup test board, ready for review
2025-01-21 Finished lcbringup, ready to order
2025-03-12 Lots of initial firmware work on lcbringup test setup
2025-03-12 Initial RTL skeleton
2025-05-04 Initial firmware is now pingable
2025-05-05 Initial CLI and SSH integration
2025-05-12 Added software workaround for line card LED1 errata
2025-05-16 Initial version of LineCardControlRegisters and LineCardInputBuffering, imported some test pcaps
2025-05-19 Initial work on LineCardFIFOReader, imported MACAddressTable
2025-05-20 Continued work on initial RX FIFO
2025-05-20 Line card: fixed typo in component value and alternate pinmux mode
2025-05-21 Continued initial FIFO read logic
2025-05-21 Input FIFO is close to capable of forwarding. No backpressure support and huge gaps due to latency of URAM
2025-05-21 Continued work on FIFO reader. Reduced latency but still have a 5-cycle gap
2025-05-22 Initial work on mac table integration
2025-05-22 AXI-stream conversion for MAC address table lookup side bus
2025-05-22 AXI-ified mac lookup table
2025-05-23 Initial work on prefetch for line card FIFO
2025-05-23 Added FWD_STATE_TAIL so we can start doing URAM operations once prefetch finishes. Still 2 cycle dead time we might be able to optimize
2025-05-23 AXI integration for synthesis
2025-05-24 More work on LineCardInputBuffering, fixed some bugs
2025-05-24 Began timing optimizations to FIFO read code
2025-05-24 More refactoring, removed redundant meta_wr_ signals
2025-05-25 Fixed more bugs, now seems to be working for BPDUs
2025-05-25 Continued debugging ingress buffering
2025-05-27 Added FIFO stuck detection while chasing CDC timing issues
2025-05-27 Port VLAN and length now should be using LUTRAM (not yet verified in implementation)
2025-05-27 Fixed bug causing extra beat with TLAST set and TSTRB=0 at end of a frame
2025-05-27 port_src_mac_lo is now using LUTRAM too
2025-05-28 Added canStartForwarding gate to prevent trying to forward a new frame in some situations while the previous frame was still busy
2025-05-28 Added FIFO to output of LineCardInputBuffering to allow backpressure from fabric
2025-05-28 Initial implementation of LineCardDestinationDecoder
2025-05-29 Initial version of mainboard power budget
2025-05-29 Initial protocase enclosure skeleton
2025-05-29 Continued initial enclosure design experiments
2025-05-29 Updated enclosure design as stainless with side by side line cards and uplink at the right
2025-05-30 Initial work on dual-sfp28 board
2025-05-30 Continued chassis design, added PDU and IBC but not in final positions
2025-05-31 Initial versino of dual-sfp28 is fully routed and ready for review
2025-06-01 Updated dual-sfp28 board with final config for fab
2025-06-01 Initial work on switch engine schematic
2025-06-01 Continued initial schematic work on switch engine
2025-06-02 First iteration of main board PCB schematic is now passing ERC
2025-06-02 Finished schematic review
2025-06-02 Added footprints and created initial skeleton of layout
2025-06-03 Initial rough floorplan
2025-06-03 Initial rough FPGA power routing
2025-06-03 Initial power routing of MCU, breakout for FMC signals on FPGA
2025-06-04 Initial routing progress on RGMII and FMC
2025-06-04 Lots of progress routing ARC6s
2025-06-05 Progress on GTY routing
2025-06-05 Continued routing southwest area
2025-06-05 More tweaking to SERDES routing
2025-06-05 Initial floorplanning of northwest area
2025-06-05 More routing in northwest area
2025-06-06 Continued layout of MCU area, added cutout for fan
2025-06-06 More progress on PHY layout
2025-06-07 Continued routing main MCU and FPGA support parts, hooked up part of boot flash
2025-06-07 Routing cleanup around FMC, still needs a lot more
2025-06-08 Lots of routing cleanup around MCU
2025-06-09 Rerouted FMC to not need any mid-span vias
2025-06-09 Routing mostly in southeast corner
2025-06-11 Routed line card management low-speed signals
2025-06-11 Started routing supervisor area in northeast corner
2025-06-11 More work on supervisor area
2025-06-12 Continued right side layout, basically everything done except power supply
2025-06-12 Began layout of power supply area
2025-06-12 Initial floorplanning of PSU
2025-06-13 Updating file: switch-engine.kicad_pcb with current completely routed design
2025-06-14 Continued power plane layout
2025-06-14 Hopefully-finished internal layer power plane layout, DRC clean. Still needs outer layer power pours and stitching vias
2025-06-14 Added more top layer power fills, lots of stitching vias around serdes
2025-06-15 Near-final layout after a bunch more tweaking. Still needs stitching vias around low speed stuff
2025-06-18 Initial PCB simulations for switch engine
2025-06-19 Initial simulations of bga launch and related
2025-06-20 More work on connector launch design
2025-06-20 Removed ARF6 front side simulations other than the final layout we plan to use
2025-07-01 Added lots more sims
2025-07-01 Deleted a bunch of sims that didn't give good results
2025-07-02 Updated simulations for switch-3 import cycle
2025-07-02 Added more switch3 sims
2025-07-03 Updated embedded-utils
2025-07-03 Linker script: added FPGA QSPI and others
2025-07-03 BSP: add QSPI flash
2025-07-03 Initial fine tuning of QSGMII SERDES equalizer taps
2025-07-05 Initial refactoring of VSC8512 driver to be more readable and OO
2026-06-11 Moved simulations to old folder
2026-06-11 Pushing current kicad/vivado stuff
2026-06-14 Initial version with a zillion sims
2026-06-14 Removed a bunch of sims we no longer are using
2026-06-16 Continued layout tweaks on diffpairs
2026-06-16 Continued simulation work
2026-06-16 More simulations
2026-06-16 Removed a bunch of simulations we no longer use
2026-06-17 More work on front side simulation
2026-06-20 Continued SERDES SI tuning
2026-06-20 Added SFP28 TX0 simulation
2026-06-21 Continued SFP28 launch modeling
2026-06-22 Continued simulation work on ARC6 launches
2026-06-22 Added gitignore
2026-06-24 Continued re-layout of top layer GTY tracks
